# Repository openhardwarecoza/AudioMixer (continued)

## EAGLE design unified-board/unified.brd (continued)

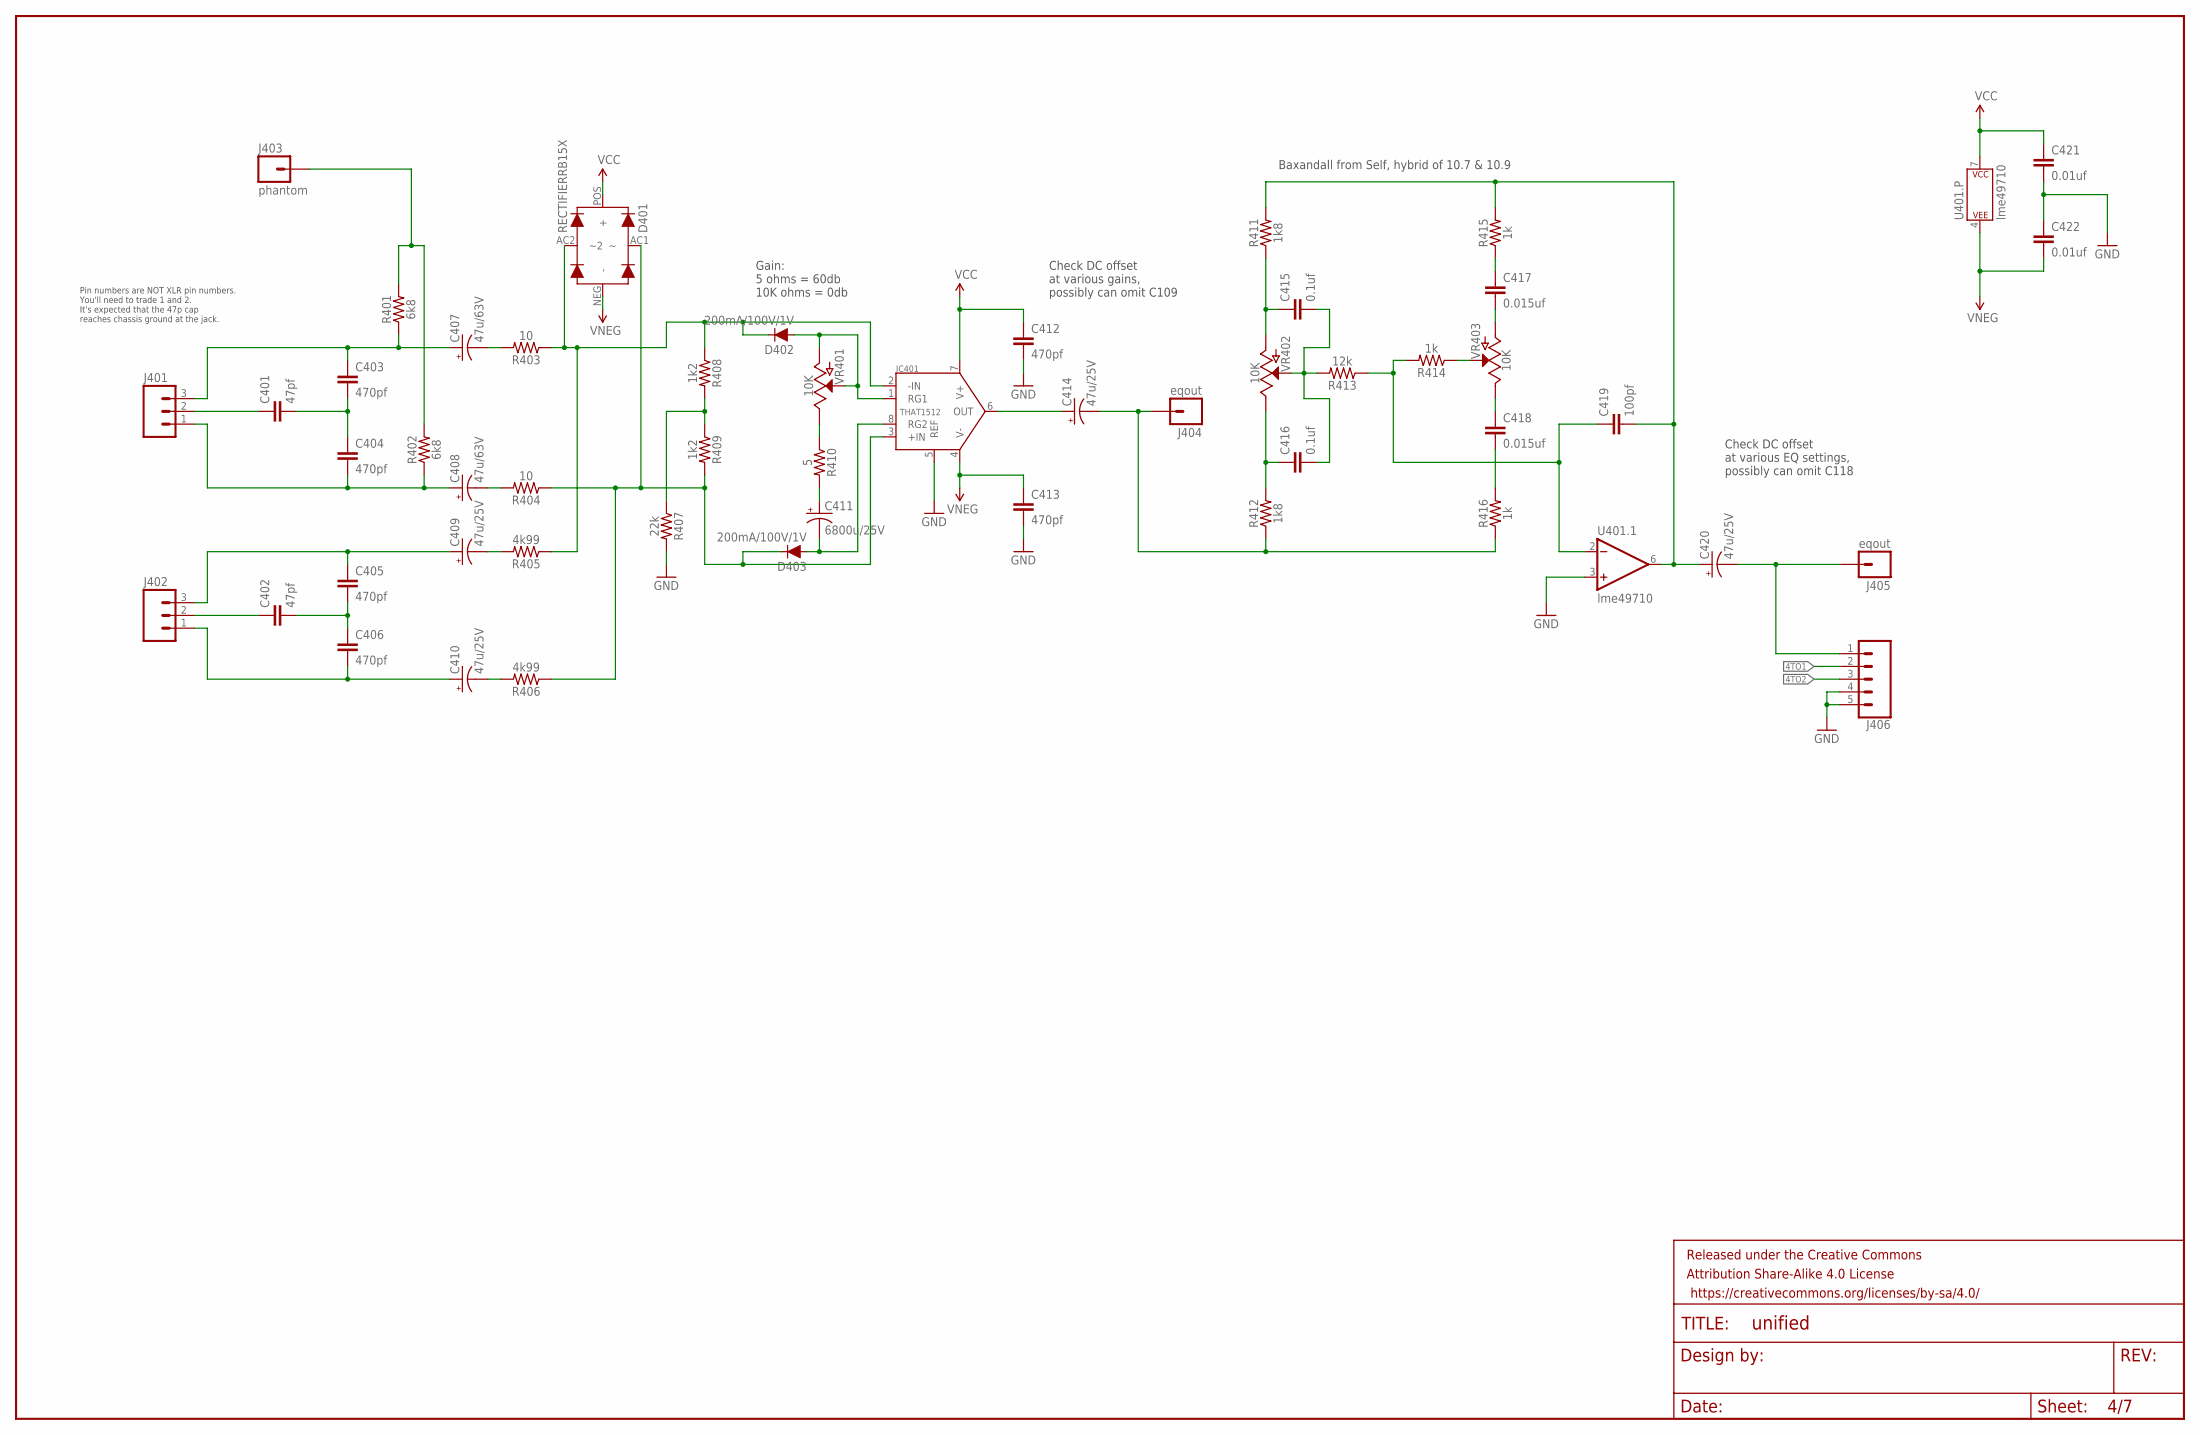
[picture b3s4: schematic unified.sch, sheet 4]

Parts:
C401, C402: 47pf; CAP-KEMET-GM-2.54LS
C403, C404, C405, C406, C412, C413: 470pf; CAP-KEMET-GM-2.54LS
C407, C408: 47u/63V; CAP-PANA-2LS-6DIAM
C409, C410, C414, C420: 47u/25V; CAP-PANA-2LS-5DIAM
C411: 6800u/25V; CAP-PANA-5LS-12.5DIAM
C415, C416: 0.1uf; WIMA-MKS2-2.5X7.2
C417, C418: 0.015uf; WIMA-MKS2-2.5X7.2
C419: 100pf; CAP-KEMET-GM-2.54LS
C421, C422: 0.01uf; WIMA-MKS2-2.5X7.2
D401: RECTIFIERRB15X; SM-RECTIFIER
D402, D403: 200mA/100V/1V; DIODE-1N4148
FRAME401: FRAME-LEDGER; CREATIVE_COMMONS
IC401: THAT1512; DIP08-KIT
J401, J402: M031X03_NO_SILK; 1X03_NO_SILK@1
J403: phantom; 1X01NS-KIT
J404, J405: eqout; 1X01NS-KIT
J406: CONN_05PTH_LONGPADS; 1X05_LONGPADS
R401, R402: 6k8; AXIAL-0.3
R403, R404: 10; AXIAL-0.3
R405, R406: 4k99; AXIAL-0.3
R407: 22k; AXIAL-0.3
R408, R409: 1k2; AXIAL-0.3
R410: 5; AXIAL-0.3
R411, R412: 1k8; AXIAL-0.3
R413: 12k; AXIAL-0.3
R414, R415, R416: 1k; AXIAL-0.3
U401: lme49710; DIP08-KIT
VR401: 10K; ROT-SW-POT
VR402, VR403: 10K; ALPHA-RV24AF40-POT

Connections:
4TO1: J406.2; also elsewhere on the board
4TO2: J406.3; also elsewhere on the board
EQ4OUT: C420.NEG (-), J405.1, J406.1
GND: C412.P$2 (2), C413.P$2 (2), C421.P$2 (2), C422.P$1 (1), IC401.5 (REF), J406.4, J406.5, R407.P$2 (2), U401.3 (+IN); also elsewhere on the board
unnamed: C414.NEG (-), J404.1, R412.P$1 (1), R416.P$1 (1)
unnamed: C415.P$1 (1), R411.P$1 (1), VR402.CCW (A)
unnamed: C416.P$1 (1), R412.P$2 (2), VR402.CW (E)
unnamed: R414.P$1 (1), VR403.WIP (S)
unnamed: C415.P$2 (2), C416.P$2 (2), R413.P$2 (2), VR402.WIP (S)
unnamed: C418.P$2 (2), R416.P$2 (2)
unnamed: C417.P$1 (1), R415.P$1 (1)
unnamed: C419.P$1 (1), R413.P$1 (1), R414.P$2 (2), U401.2 (-IN)
unnamed: C414.POS (+), IC401.6 (OUT)
unnamed: C401.P$1 (1), J401.2
unnamed: C401.P$2 (2), C403.P$2 (2), C404.P$1 (1)
unnamed: C403.P$1 (1), C407.POS (+), J401.3, R401.P$1 (1)
unnamed: C404.P$2 (2), C408.POS (+), J401.1, R402.P$1 (1)
unnamed: C408.NEG (-), R404.P$2 (2)
unnamed: J403.1, R401.P$2 (2), R402.P$2 (2)
unnamed: C407.NEG (-), R403.P$2 (2)
unnamed: R407.P$1 (1), R408.P$2 (2), R409.P$1 (1)
unnamed: C411.NEG (-), D403.A, IC401.8 (RG2)
unnamed: D402.A, IC401.1 (RG1), VR401.CCW (A), VR401.WIP (S)
unnamed: C418.P$1 (1), VR403.CW (E)
unnamed: C417.P$2 (2), VR403.CCW (A)
unnamed: R410.P$1 (1), VR401.CW (E)
unnamed: C411.POS (+), R410.P$2 (2)
unnamed: C402.P$1 (1), J402.2
unnamed: C402.P$2 (2), C405.P$2 (2), C406.P$1 (1)
unnamed: C405.P$1 (1), C409.POS (+), J402.3
unnamed: C406.P$2 (2), C410.POS (+), J402.1
unnamed: C410.NEG (-), R406.P$2 (2)
unnamed: C409.NEG (-), R405.P$2 (2)
unnamed: D401.AC2 (~2), D402.C, IC401.2 (-IN), R403.P$1 (1), R405.P$1 (1), R408.P$1 (1)
unnamed: D401.AC1, D403.C, IC401.3 (+IN), R404.P$1 (1), R406.P$1 (1), R409.P$2 (2)
unnamed: C419.P$2 (2), C420.POS (+), R411.P$2 (2), R415.P$2 (2), U401.6 (OUT)
VCC: C412.P$1 (1), C421.P$1 (1), D401.POS (+), IC401.7 (V+), U401.7 (P$V+); also elsewhere on the board
VNEG: C413.P$1 (1), C422.P$2 (2), D401.NEG (-), IC401.4 (V-), U401.4 (P$V-); also elsewhere on the board

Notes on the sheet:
Pin numbers are NOT XLR pin numbers. You'll need to trade 1 and 2. It's expected that the 47p cap reaches chassis ground at the jack.
Baxandall from Self, hybrid of 10.7 & 10.9
Gain: 5 ohms = 60db 10K ohms = 0db
Check DC offset at various gains, possibly can omit C109
Check DC offset at various EQ settings, possibly can omit C118

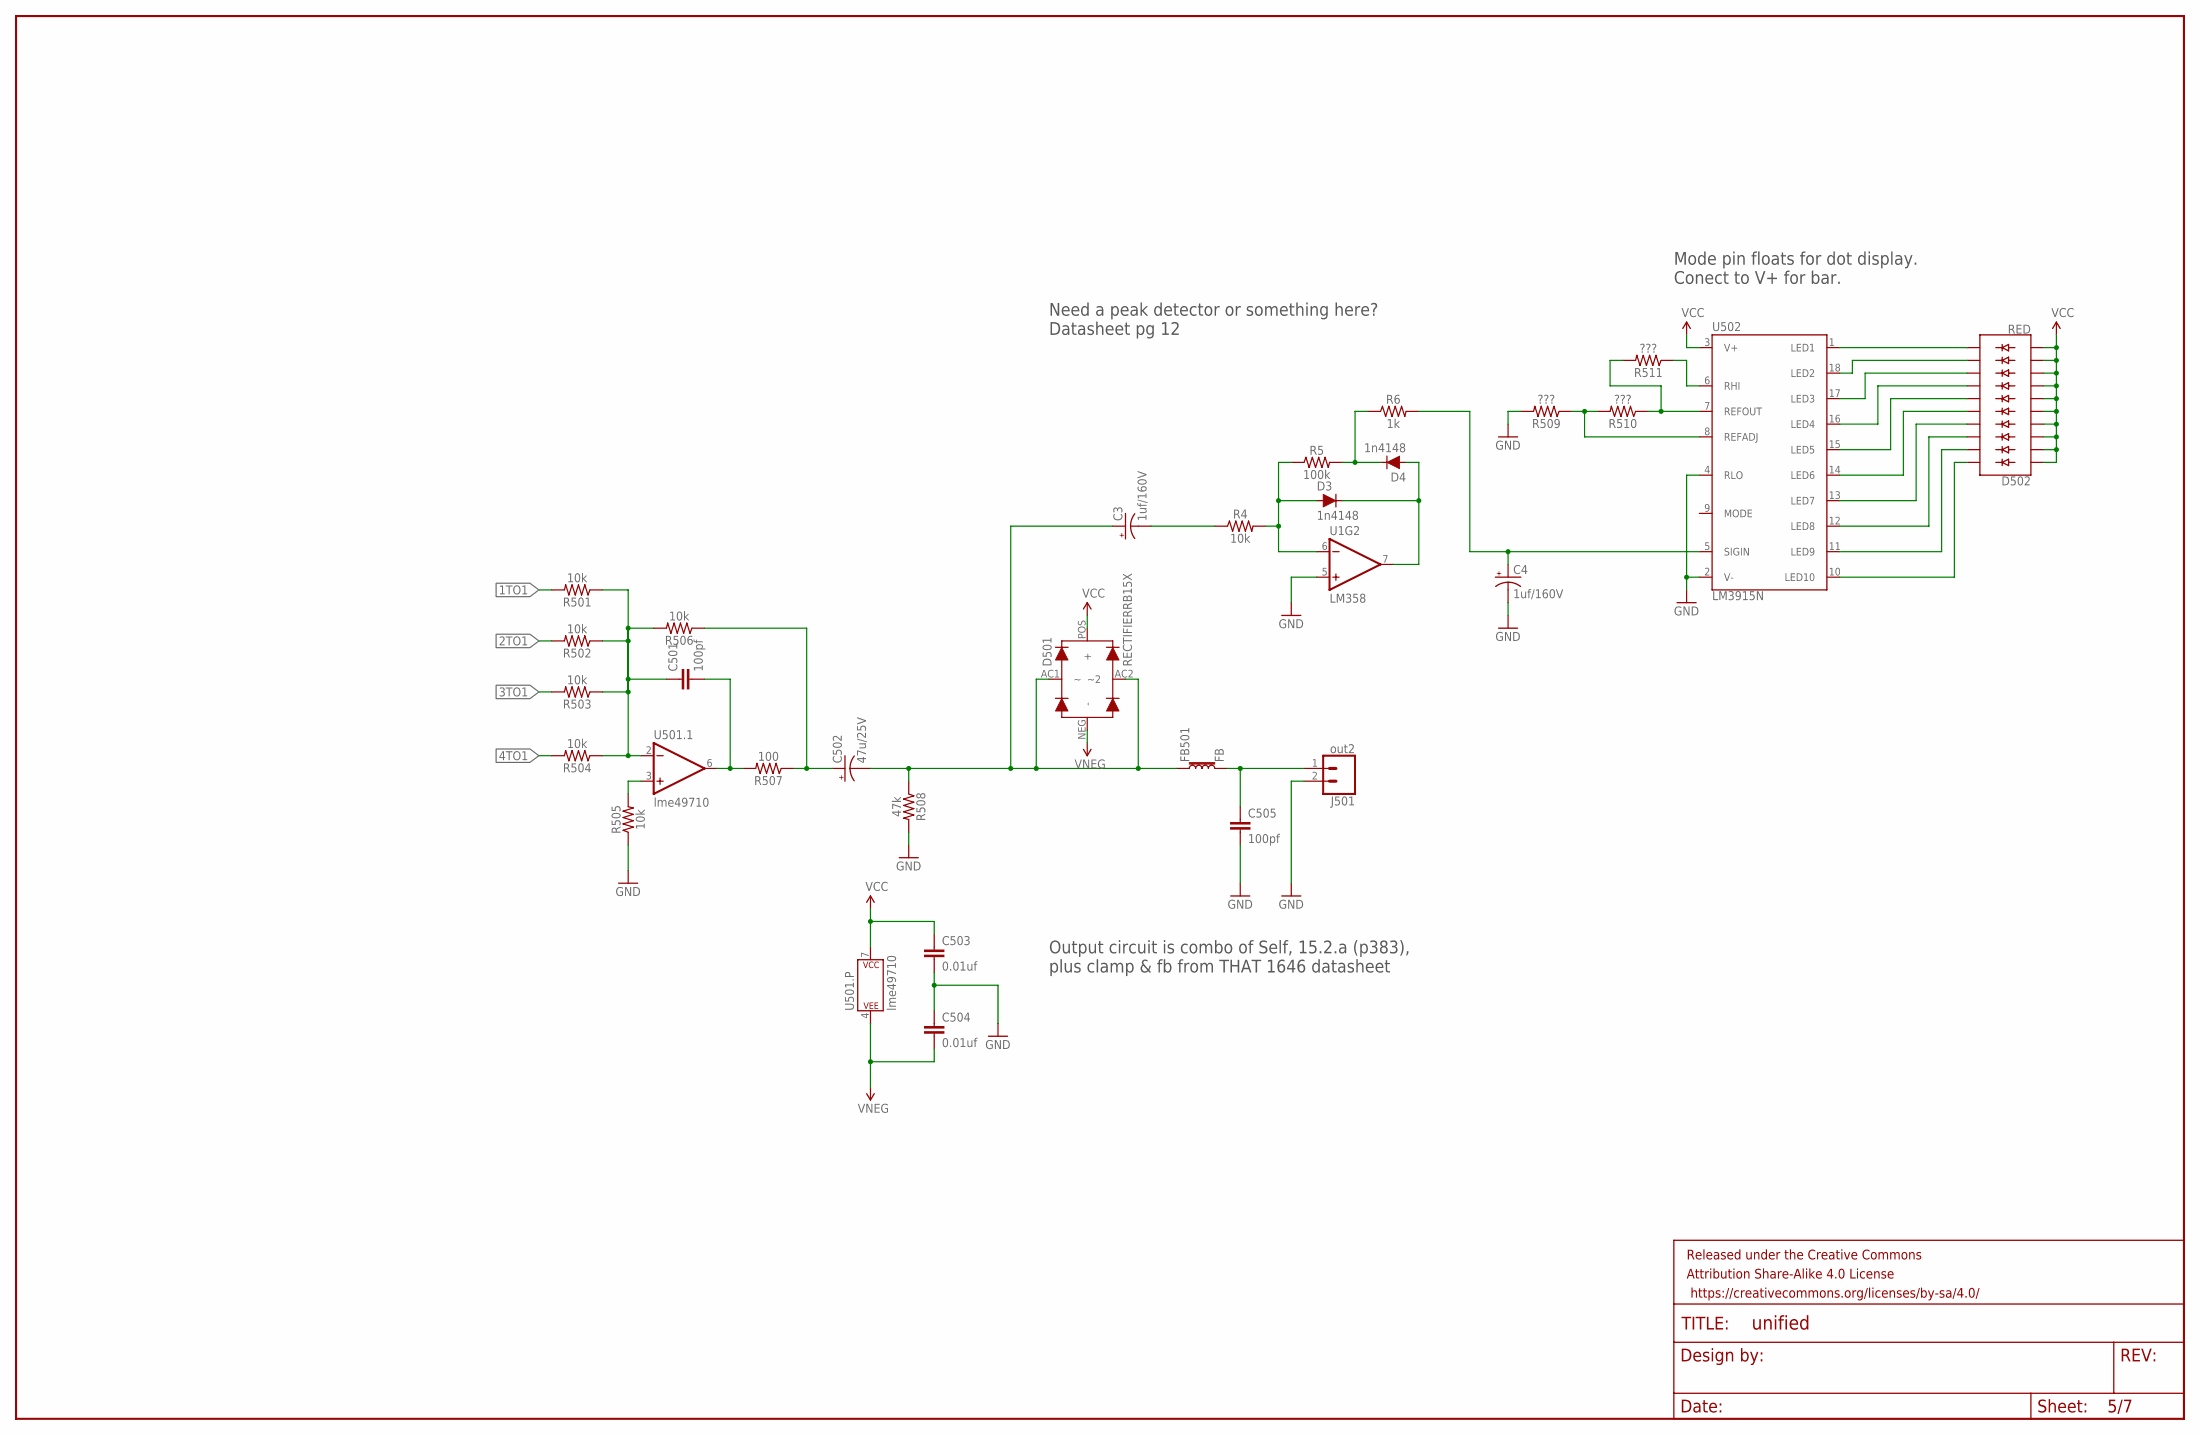
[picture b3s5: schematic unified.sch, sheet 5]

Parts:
C3, C4: 1uf/160V; CAP-PANA-2.5LS-6DIAM
C501, C505: 100pf; CAP-KEMET-GM-2.54LS
C502: 47u/25V; CAP-PANA-2LS-5DIAM
C503, C504: 0.01uf; WIMA-MKS2-2.5X7.2
D3, D4: 1n4148; DIODE-1N4148
D501: RECTIFIERRB15X; SM-RECTIFIER
D502: RED; LED_BARGRAPH_10
FB501: FB; BEAD
FRAME501: FRAME-LEDGER; CREATIVE_COMMONS
J501: out2; 1X02_LOCK_LONGPADS
R4, R501, R502, R503, R504, R505, R506: 10k; AXIAL-0.3
R5: 100k; AXIAL-0.3
R6: 1k; AXIAL-0.3
R507: 100; AXIAL-0.3
R508: 47k; AXIAL-0.3
R509, R510, R511: ???; AXIAL-0.3
U1: LM358; DIP08
U501: lme49710; DIP08-KIT
U502: LM3915N; DIL18

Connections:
1TO1: R501.P$2 (2); also elsewhere on the board
2TO1: R502.P$2 (2); also elsewhere on the board
3TO1: R503.P$2 (2); also elsewhere on the board
4TO1: R504.P$2 (2); also elsewhere on the board
GND: C4.NEG (-), C503.P$2 (2), C504.P$1 (1), C505.P$2 (2), J501.2, R505.P$1 (1), R508.P$2 (2), R509.P$2 (2), U1.5 (+IN), U502.2 (V-), U502.4 (RLO); also elsewhere on the board
HIGHEST1: D502.20 (C), U502.10 (LED10)
LOWEST1: D502.11 (C9), U502.1 (LED1)
unnamed: D3.A, R4.P$2 (2), R5.P$1 (1), U1.6 (-IN)
unnamed: D3.C, D4.A, U1.7 (OUT)
unnamed: D4.C, R5.P$2 (2), R6.P$1 (1)
unnamed: C3.NEG (-), R4.P$1 (1)
unnamed: C4.POS (+), R6.P$2 (2), U502.5 (SIGIN)
unnamed: R505.P$2 (2), U501.3 (+IN)
unnamed: C501.P$1 (1), R501.P$1 (1), R502.P$1 (1), R503.P$1 (1), R504.P$1 (1), R506.P$2 (2), U501.2 (-IN)
unnamed: C505.P$1 (1), FB501.P$2 (2), J501.1
unnamed: C3.POS (+), C502.NEG (-), D501.AC1, D501.AC2 (~2), FB501.P$1 (1), R508.P$1 (1)
unnamed: D502.12 (C8), U502.18 (LED2)
unnamed: D502.13 (C7), U502.17 (LED3)
unnamed: D502.14 (C6), U502.16 (LED4)
unnamed: D502.15 (C5), U502.15 (LED5)
unnamed: D502.16 (C4), U502.14 (LED6)
unnamed: D502.17 (C3), U502.13 (LED7)
unnamed: D502.18 (C2), U502.12 (LED8)
unnamed: D502.19 (C1), U502.11 (LED9)
unnamed: R510.P$1 (1), R511.P$2 (2), U502.7 (REFOUT)
unnamed: R509.P$1 (1), R510.P$2 (2), U502.8 (REFADJ)
unnamed: C501.P$2 (2), R507.P$2 (2), U501.6 (OUT)
unnamed: C502.POS (+), R506.P$1 (1), R507.P$1 (1)
unnamed: R511.P$1 (1), U502.6 (RHI)
VCC: C503.P$1 (1), D501.POS (+), D502.1 (A), D502.2 (A1), D502.3 (A2), D502.4 (A3), D502.5 (A4), D502.6 (A5), D502.7 (A6), D502.8 (A7), D502.9 (A8), D502.10 (A9), U501.7 (P$V+), U502.3 (V+); also elsewhere on the board
VNEG: C504.P$2 (2), D501.NEG (-), U501.4 (P$V-); also elsewhere on the board

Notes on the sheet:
Need a peak detector or something here? Datasheet pg 12
Mode pin floats for dot display. Conect to V+ for bar.
Output circuit is combo of Self, 15.2.a (p383), plus clamp & fb from THAT 1646 datasheet

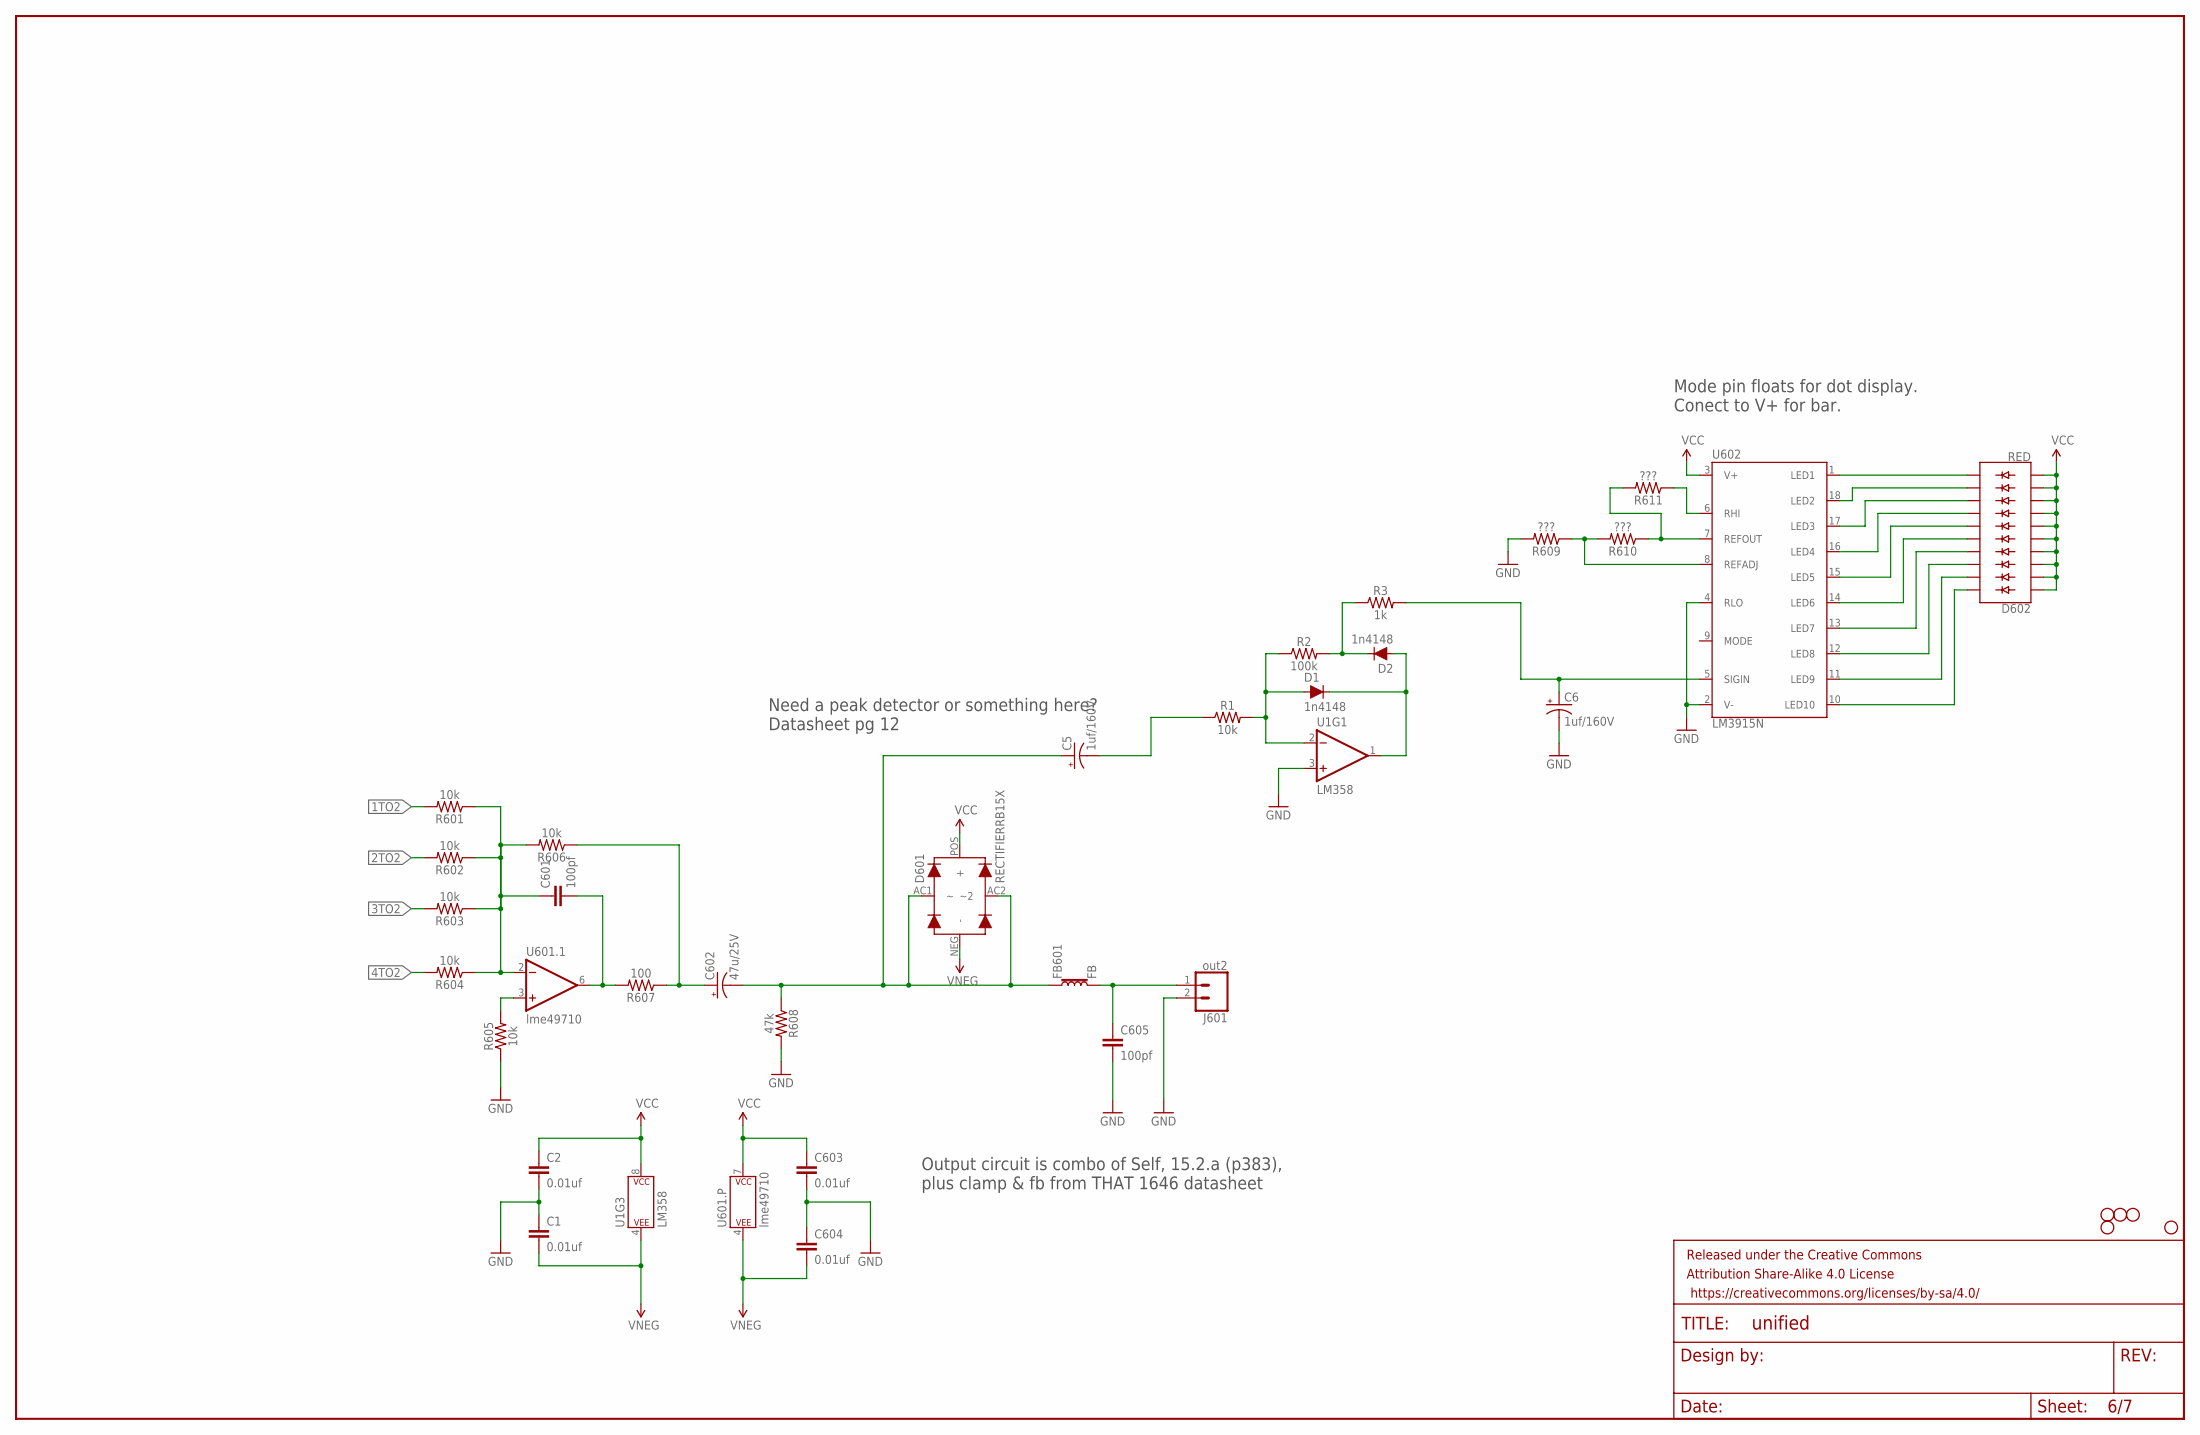
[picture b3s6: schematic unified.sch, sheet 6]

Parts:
C1, C2, C603, C604: 0.01uf; WIMA-MKS2-2.5X7.2
C5, C6: 1uf/160V; CAP-PANA-2.5LS-6DIAM
C601, C605: 100pf; CAP-KEMET-GM-2.54LS
C602: 47u/25V; CAP-PANA-2LS-5DIAM
D1, D2: 1n4148; DIODE-1N4148
D601: RECTIFIERRB15X; SM-RECTIFIER
D602: RED; LED_BARGRAPH_10
FB601: FB; BEAD
FRAME601: FRAME-LEDGER; CREATIVE_COMMONS
H601, H602, H603, H605, H612: STAND-OFF
J601: out2; 1X02_LOCK_LONGPADS
R1, R601, R602, R603, R604, R605, R606: 10k; AXIAL-0.3
R2: 100k; AXIAL-0.3
R3: 1k; AXIAL-0.3
R607: 100; AXIAL-0.3
R608: 47k; AXIAL-0.3
R609, R610, R611: ???; AXIAL-0.3
U1: LM358; DIP08
U601: lme49710; DIP08-KIT
U602: LM3915N; DIL18

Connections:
1TO2: R601.P$2 (2); also elsewhere on the board
2TO2: R602.P$2 (2); also elsewhere on the board
3TO2: R603.P$2 (2); also elsewhere on the board
4TO2: R604.P$2 (2); also elsewhere on the board
GND: C1.P$1 (1), C2.P$2 (2), C6.NEG (-), C603.P$2 (2), C604.P$1 (1), C605.P$2 (2), J601.2, R605.P$1 (1), R608.P$2 (2), R609.P$2 (2), U1.3 (+IN), U602.2 (V-), U602.4 (RLO); also elsewhere on the board
HIGHEST: D602.20 (C), U602.10 (LED10)
LOWEST: D602.11 (C9), U602.1 (LED1)
unnamed: D1.A, R1.P$2 (2), R2.P$1 (1), U1.2 (-IN)
unnamed: C605.P$1 (1), FB601.P$2 (2), J601.1
unnamed: D1.C, D2.A, U1.1 (OUT)
unnamed: C5.POS (+), C602.NEG (-), D601.AC1, D601.AC2 (~2), FB601.P$1 (1), R608.P$1 (1)
unnamed: C602.POS (+), R606.P$1 (1), R607.P$1 (1)
unnamed: R605.P$2 (2), U601.3 (+IN)
unnamed: C601.P$2 (2), R607.P$2 (2), U601.6 (OUT)
unnamed: C601.P$1 (1), R601.P$1 (1), R602.P$1 (1), R603.P$1 (1), R604.P$1 (1), R606.P$2 (2), U601.2 (-IN)
unnamed: D2.C, R2.P$2 (2), R3.P$1 (1)
unnamed: C6.POS (+), R3.P$2 (2), U602.5 (SIGIN)
unnamed: D602.12 (C8), U602.18 (LED2)
unnamed: D602.13 (C7), U602.17 (LED3)
unnamed: D602.14 (C6), U602.16 (LED4)
unnamed: D602.15 (C5), U602.15 (LED5)
unnamed: D602.16 (C4), U602.14 (LED6)
unnamed: D602.17 (C3), U602.13 (LED7)
unnamed: D602.18 (C2), U602.12 (LED8)
unnamed: D602.19 (C1), U602.11 (LED9)
unnamed: R610.P$1 (1), R611.P$2 (2), U602.7 (REFOUT)
unnamed: R609.P$1 (1), R610.P$2 (2), U602.8 (REFADJ)
unnamed: R611.P$1 (1), U602.6 (RHI)
unnamed: C5.NEG (-), R1.P$1 (1)
VCC: C2.P$1 (1), C603.P$1 (1), D601.POS (+), D602.1 (A), D602.2 (A1), D602.3 (A2), D602.4 (A3), D602.5 (A4), D602.6 (A5), D602.7 (A6), D602.8 (A7), D602.9 (A8), D602.10 (A9), U1.8 (P$V+), U601.7 (P$V+), U602.3 (V+); also elsewhere on the board
VNEG: C1.P$2 (2), C604.P$2 (2), D601.NEG (-), U1.4 (P$V-), U601.4 (P$V-); also elsewhere on the board

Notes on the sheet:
Need a peak detector or something here? Datasheet pg 12
Mode pin floats for dot display. Conect to V+ for bar.
Output circuit is combo of Self, 15.2.a (p383), plus clamp & fb from THAT 1646 datasheet

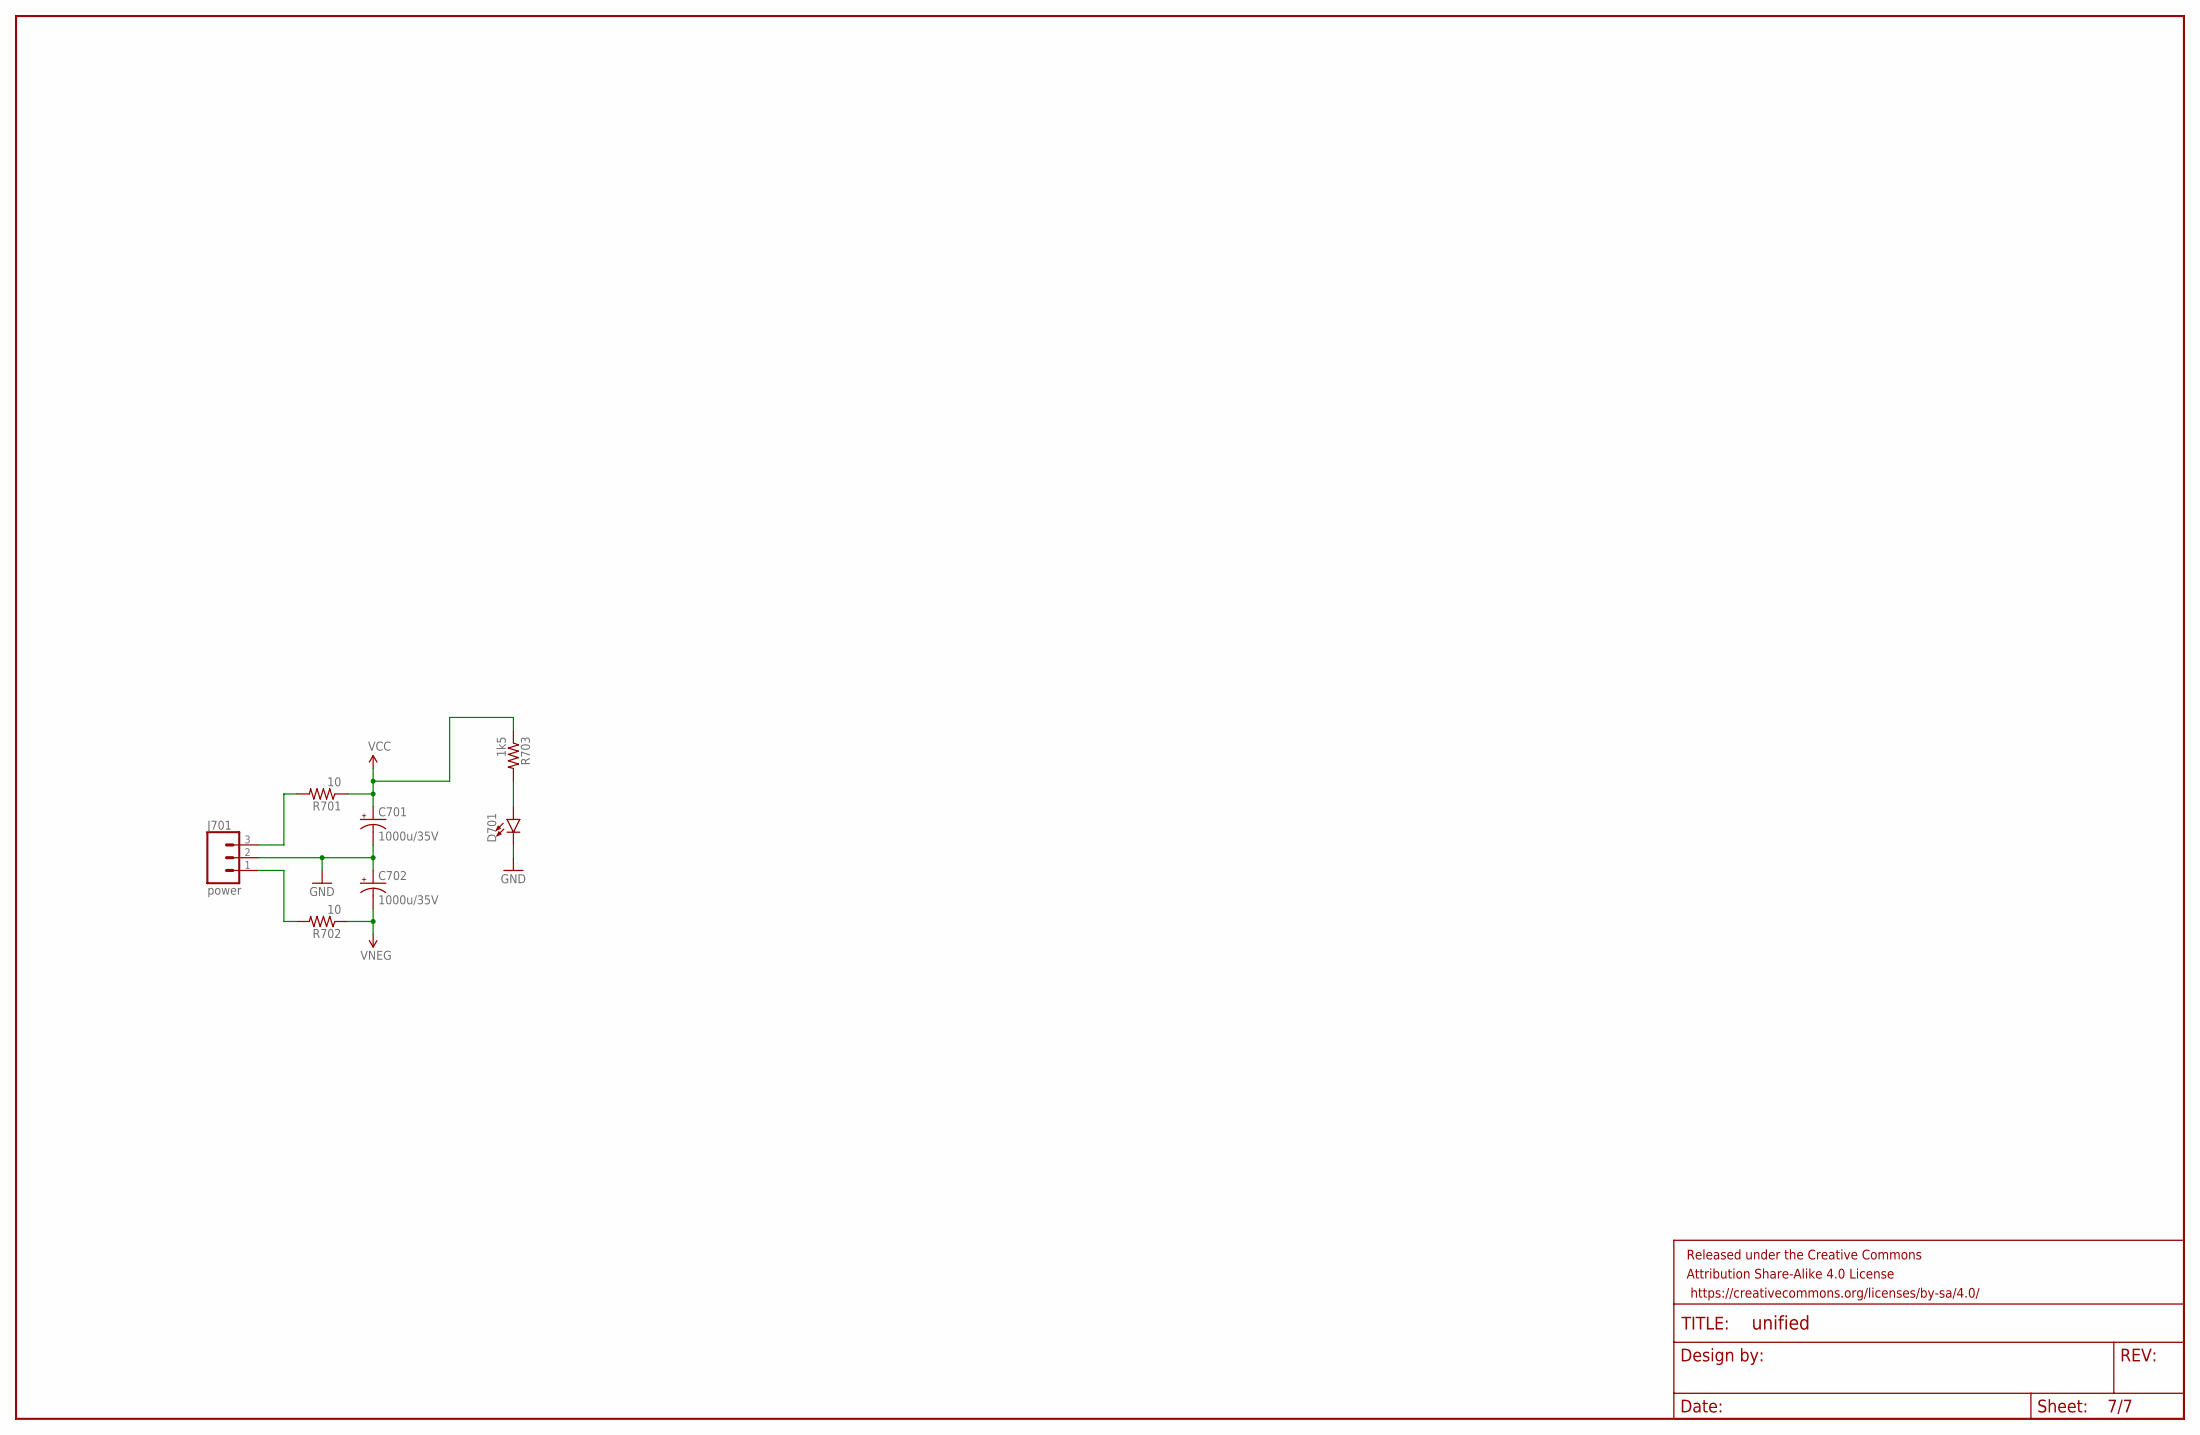
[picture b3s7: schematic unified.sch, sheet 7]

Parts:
C701, C702: 1000u/35V; CAP-PANA-5LS-12.5DIAM
D701: LED5MM; LED_5MM
FRAME701: FRAME-LEDGER; CREATIVE_COMMONS
J701: power; MOLEX-1X3_LOCK
R701, R702: 10; AXIAL-0.3
R703: 1k5; AXIAL-0.3

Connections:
GND: C701.NEG (-), C702.POS (+), D701.K (C), J701.2; also elsewhere on the board
unnamed: J701.1, R702.P$2 (2)
unnamed: J701.3, R701.P$2 (2)
unnamed: D701.A, R703.P$2 (2)
VCC: C701.POS (+), R701.P$1 (1), R703.P$1 (1); also elsewhere on the board
VNEG: C702.NEG (-), R702.P$1 (1); also elsewhere on the board

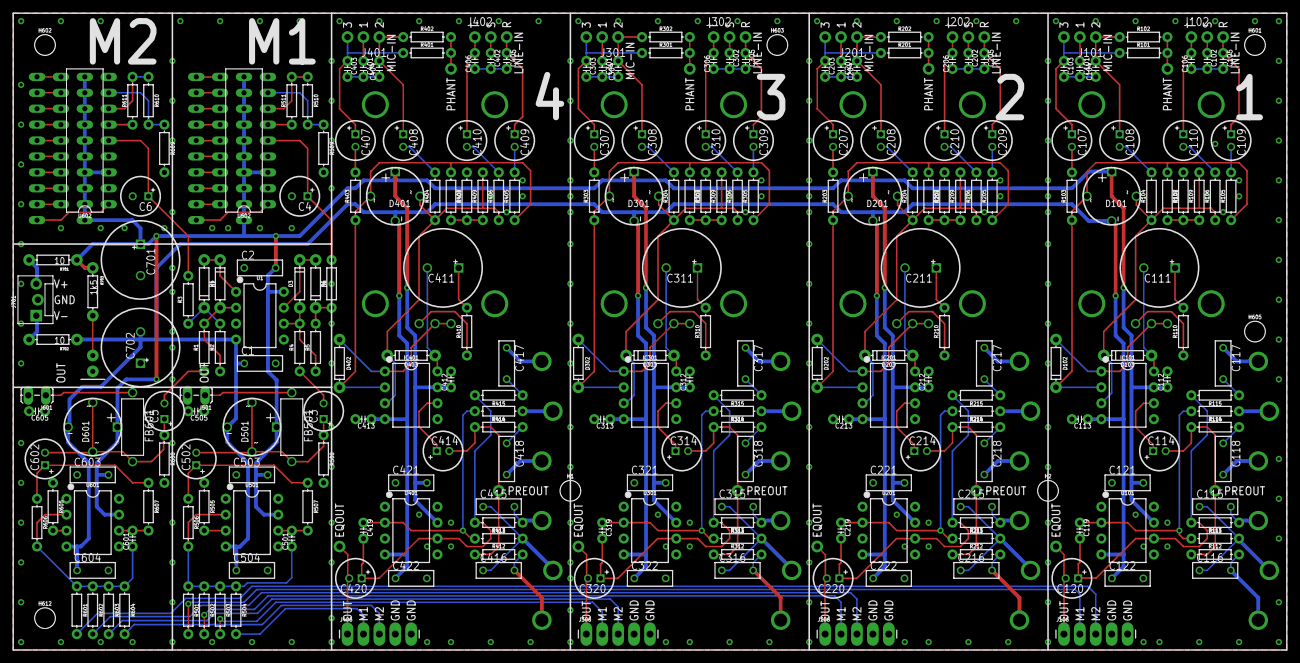
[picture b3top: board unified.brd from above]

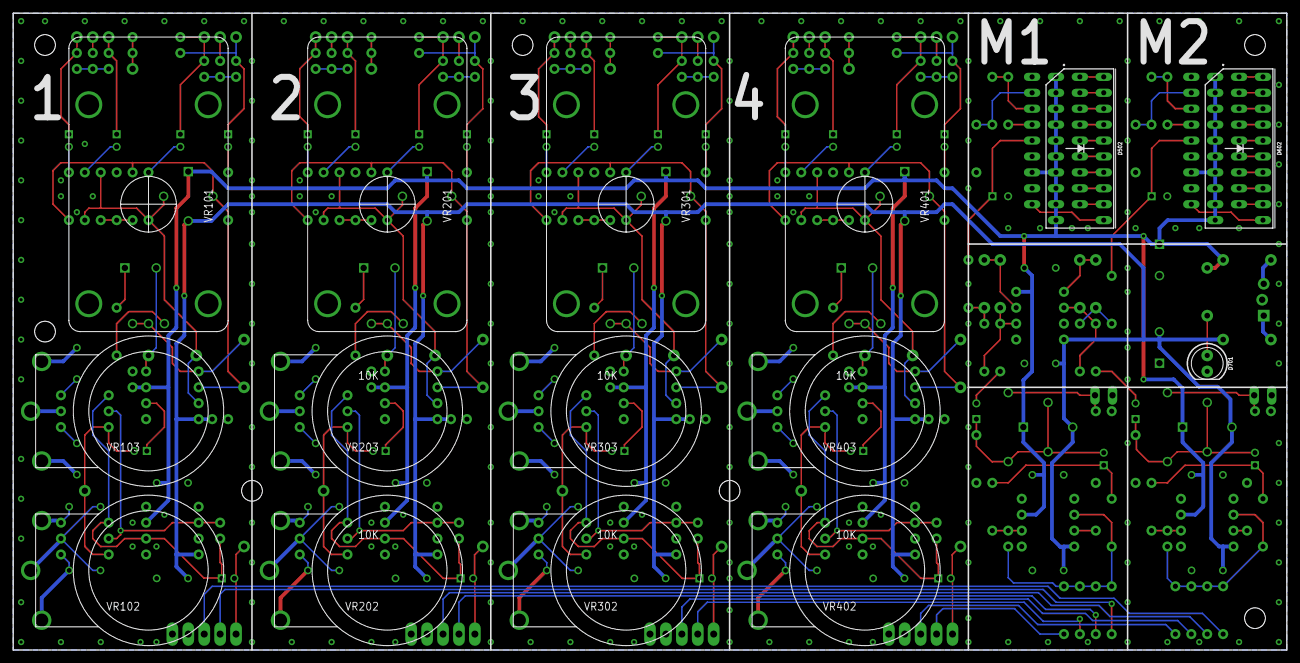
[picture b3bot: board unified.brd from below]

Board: 2 copper layers, 203.2 x 101.6 mm, 290 parts (15 on the bottom side), 194 nets.

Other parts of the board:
H1, H2: STAND-OFF

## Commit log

2021-03-29 Start
